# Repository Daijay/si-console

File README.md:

# SI Console

SI Console stands for Super Intelligence Console. It is a physical console that allows agentic orchestration. There is a push to talk mic, an English/Chinese toggle, LEDs, a 5 inch status screen and a monitor dashboard. This hardware project showcases the physical process of agentic orchestration, not just something that lives in your computer.

## How to use it
Press and hold the push to talk button and speak. The agents work, the LEDs show which agent is active, and the 5 inch screen shows status. Risky actions wait for you to press the green button. The red button rejects. The kill switch freezes everything. The toggle switches between English and Chinese.

## Why I made it
I wanted agents that can't just run wild. Most AI agents live in a window on your computer, and if something goes wrong, the same software that's running away has to be the thing that stops it. A software approve button has that problem. If the agent or a prompt injection controls the software, it can press the button itself. So I put approval on a real button on its own wire. Nothing in the software can press it. The kill switch is a latching switch on its own pin, and the orchestrator stops everything when it is flipped. Right now that stop is read by software, so I want to wire it in series with the green button so approval is physically impossible while the kill switch is engaged. It also makes the demo physical, because a visitor can press the big green button themselves. For low-risk actions like read-only searches, I plan to add approve on the touchscreen, so risky things need the real button and safe things stay fast. This is my first hardware project.

## Design

- Raspberry Pi 5 8GB, ULN2003 driver for the LEDs, GPIO buttons, 5 inch HDMI status screen, MSI portable monitor
- Open frame on clear laser-cut acrylic, 2 sheets. The circuit is on a custom PCB, with perfboard as a backup.
- Pin map: docs/GPIO_PIN_MAP.md

- PCB source: pcb/

## Files
- CAD assembly (STEP): blueprints/R5/si_console_assembly_R5.step
- Per-part STEP files: blueprints/R5/step/
- Fusion source: [Fusion archive (R5)](cad/si_console_R5.f3d)
- Firmware and agent code: code/
- BOM with links: bom/BOM.csv (about USD 719 including tax, the main monitor was bought by me and is not in the fundable total)

## Team
- Jayden: system, hardware, CAD, integration
- Christopher: software architecture and agent orchestration

## How I used AI
I came up with the idea and made the main decisions: the hardware, the open-frame design, and what to cut or add to stay on budget. I used AI for brainstorming, looking up part specs and prices, and Claude Code to generate first versions of the CAD scripts, wiring diagram, code and tests. I then reviewed what came out and decided what to change, keep or throw away. For example, I scrapped the boxed case because it hid the electronics.

## What's next
Christopher and I are each logging 5 to 6 hours a day while balancing IB. The plan is to get the design approved, order the parts, and finish the build by December 8, then take it to Maker Faire Shenzhen on December 11 to 14. We both want to travel there, show the project, and see Shenzhen. My biggest worry is running out of time to submit, especially waiting on design approval and parts shipping before the build.

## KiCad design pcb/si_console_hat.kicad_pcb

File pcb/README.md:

# SI Console HAT

A 2-layer, 1.6 mm Raspberry Pi 5 HAT-style carrier board (65 x 56.5 mm) that replaces the perfboard: ULN2003A LED driver, four LED resistors and a labelled screw terminal for every off-board wire. Pins follow `docs/GPIO_PIN_MAP.md`; no GPIO changed. The perfboard is the fallback, so the R5 wiring diagram (same electrical nets) was not changed.

## Connectors

| Ref | Label | Pins |
| --- | --- | --- |
| J2 | COORD | + (5 V through 150 ohm), - (OUT1, GPIO5) |
| J3 | AGENT 1 | + (100 ohm), - (OUT2, GPIO6) |
| J4 | AGENT 2 | + (100 ohm), - (OUT3, GPIO13) |
| J5 | GUARD | + (220 ohm), - (OUT4, GPIO19) |
| J6 | GREEN | SW (GPIO17), GND, L+ (5 V), L- (OUT5, GPIO20) |
| J7 | RED | SW (GPIO27), GND, L+ (5 V), L- (OUT6, GPIO21) |
| J8 | KILL | SW (GPIO22), GND, IL, IL (second NC contact, optional) |
| J9 | PTT | SW (GPIO23), GND |
| J10 | LANG | SW (GPIO24), GND |

## Optional kill interlock (off as built)

JP1 is closed and JP2 is open. To make the kill switch physically block approval, wire its second NC contact to the two IL terminals, **cut JP1**, then **solder JP2**. The contact is then in series with the green button signal. Cutting JP1 alone leaves the green button dead.

## Checks (KiCad 9.0.8)

- ERC: 0 errors, 0 warnings.
- DRC with schematic parity: 0 violations, 0 unconnected, 0 footprint errors.
- JLCPCB 2-layer rules in the .kicad_pro: 0.127 mm minimum track and clearance, 0.3 mm via drill, 0.45 mm via, 0.5 mm hole to hole, 0.3 mm copper to edge.
- `python pcb/check_nets.py`: 25 nets match `gpio_map.py`.
- Routed with Freerouting 2.5.0.

## Order from JLCPCB

1. Upload `gerbers.zip` at https://cart.jlcpcb.com/quote
2. 2 layers, 65 x 56.5 mm, qty 5, 1.6 mm, 1 oz, HASL (with lead).
3. Shipping to Canada: Global Standard Direct Line.
4. Quoted 2026-11-25 by dimensions (no file uploaded): US$4.00 boards + US$6.84 shipping = US$10.84, CAD 15.50 at 1.4296. Lead-free HASL adds US$1.20. Taxes and duties not included.

## Assembly

Solder resistors, DIP socket, then terminals. J1 is an extra-tall 2x20 female header soldered on the **underside**; trim the long pins. Mount on 16 mm M2.5 standoffs. Insert the ULN2003AN with its notch matching the silkscreen.

Optional JLCPCB assembly: `jlcpcb_bom.csv` and `jlcpcb_cpl.csv`. J1 is left out (hand fit). The DIP socket has no LCSC number yet. Check part rotations in the JLCPCB preview.

## Not verified

No board has been made or tested. Gerbers were not uploaded to JLCPCB. Active Cooler clearance is from drawings only (cooler 13.7 mm overall, header gives about 16 mm). Check that the kill switch has two NC contacts. The HAT is not modelled in the CAD. There is no HAT ID EEPROM.

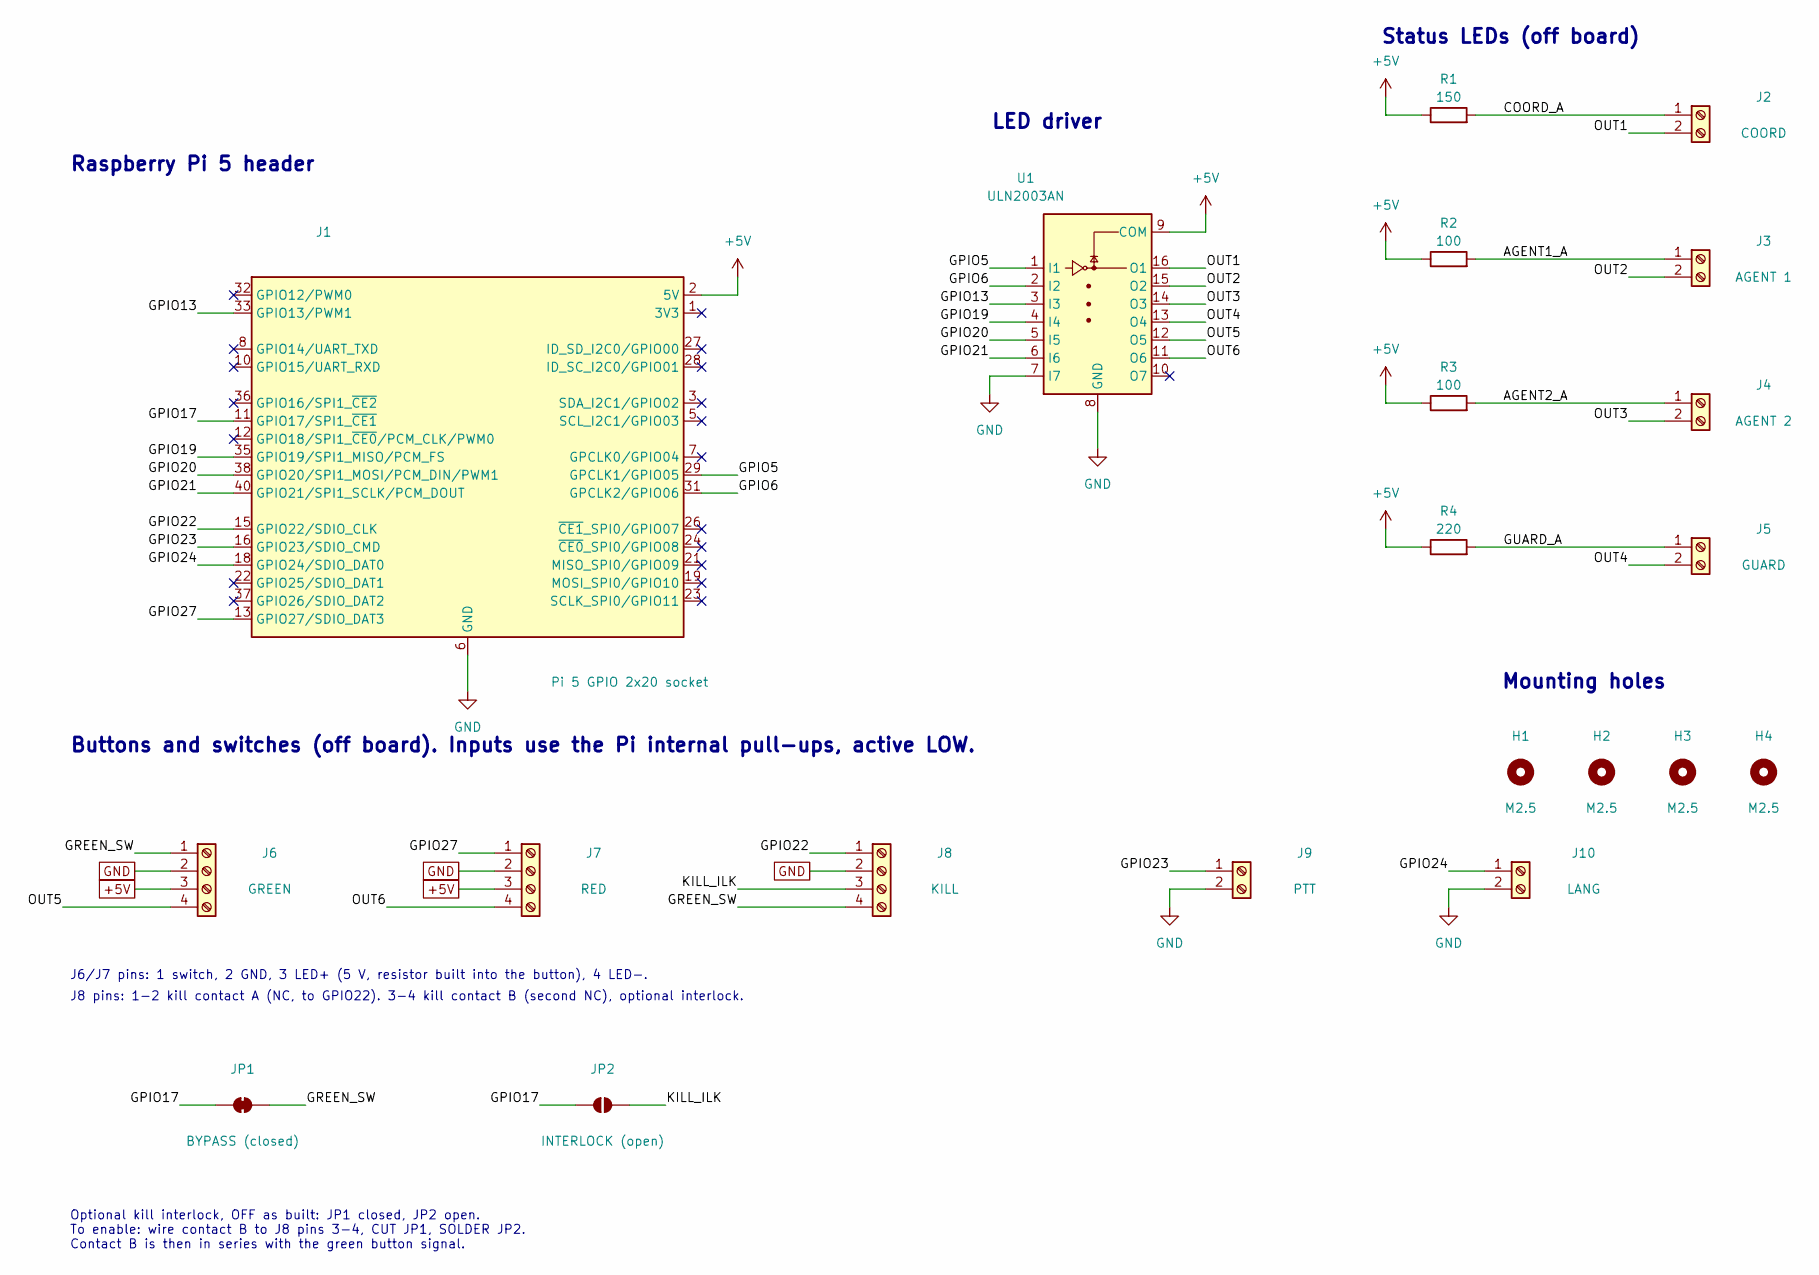
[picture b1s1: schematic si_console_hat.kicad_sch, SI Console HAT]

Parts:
H1, H2, H3, H4: M2.5; MountingHole_2.7mm_M2.5
J1: Pi 5 GPIO 2x20 socket; PinSocket_2x20_P2.54mm_Vertical; MPN Adafruit extra tall 2x20 header
J2: COORD; TerminalBlock_Phoenix_PT-1,5-2-3.5-H_1x02_P3.50mm_Horizontal; MPN Phoenix 1984617
J3: AGENT 1; TerminalBlock_Phoenix_PT-1,5-2-3.5-H_1x02_P3.50mm_Horizontal; MPN Phoenix 1984617
J4: AGENT 2; TerminalBlock_Phoenix_PT-1,5-2-3.5-H_1x02_P3.50mm_Horizontal; MPN Phoenix 1984617
J5: GUARD; TerminalBlock_Phoenix_PT-1,5-2-3.5-H_1x02_P3.50mm_Horizontal; MPN Phoenix 1984617
J6: GREEN; TerminalBlock_Phoenix_PT-1,5-4-3.5-H_1x04_P3.50mm_Horizontal; MPN Phoenix 1984633
J7: RED; TerminalBlock_Phoenix_PT-1,5-4-3.5-H_1x04_P3.50mm_Horizontal; MPN Phoenix 1984633
J8: KILL; TerminalBlock_Phoenix_PT-1,5-4-3.5-H_1x04_P3.50mm_Horizontal; MPN Phoenix 1984633
J9: PTT; TerminalBlock_Phoenix_PT-1,5-2-3.5-H_1x02_P3.50mm_Horizontal; MPN Phoenix 1984617
J10: LANG; TerminalBlock_Phoenix_PT-1,5-2-3.5-H_1x02_P3.50mm_Horizontal; MPN Phoenix 1984617
JP1: BYPASS (closed); SolderJumper-2_P1.3mm_Bridged_Pad1.0x1.5mm
JP2: INTERLOCK (open); SolderJumper-2_P1.3mm_Open_Pad1.0x1.5mm
R1: 150; R_Axial_DIN0207_L6.3mm_D2.5mm_P10.16mm_Horizontal
R2, R3: 100; R_Axial_DIN0207_L6.3mm_D2.5mm_P10.16mm_Horizontal
R4: 220; R_Axial_DIN0207_L6.3mm_D2.5mm_P10.16mm_Horizontal
U1: ULN2003AN; DIP-16_W7.62mm_Socket; MPN ULN2003AN in DIP-16 socket

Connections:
+5V: J1.2 (5V), J1.4 (5V), J6.3, J7.3, R1.1, R2.1, R3.1, R4.1, U1.9 (COM)
/AGENT1_A: J3.1, R2.2
/AGENT2_A: J4.1, R3.2
/COORD_A: J2.1, R1.2
/GPIO5: J1.29 (GPCLK1/GPIO05), U1.1 (I1)
/GPIO6: J1.31 (GPCLK2/GPIO06), U1.2 (I2)
/GPIO13: J1.33 (GPIO13/PWM1), U1.3 (I3)
/GPIO17: J1.11 (GPIO17/SPI1_~CE1), JP1.1 (A), JP2.1 (A)
/GPIO19: J1.35 (GPIO19/SPI1_MISO/PCM_FS), U1.4 (I4)
/GPIO20: J1.38 (GPIO20/SPI1_MOSI/PCM_DIN/PWM1), U1.5 (I5)
/GPIO21: J1.40 (GPIO21/SPI1_SCLK/PCM_DOUT), U1.6 (I6)
/GPIO22: J1.15 (GPIO22/SDIO_CLK), J8.1
/GPIO23: J1.16 (GPIO23/SDIO_CMD), J9.1
/GPIO24: J1.18 (GPIO24/SDIO_DAT0), J10.1
/GPIO27: J1.13 (GPIO27/SDIO_DAT3), J7.1
/GREEN_SW: J6.1, J8.4, JP1.2 (B)
/GUARD_A: J5.1, R4.2
/KILL_ILK: J8.3, JP2.2 (B)
/OUT1: J2.2, U1.16 (O1)
/OUT2: J3.2, U1.15 (O2)
/OUT3: J4.2, U1.14 (O3)
/OUT4: J5.2, U1.13 (O4)
/OUT5: J6.4, U1.12 (O5)
/OUT6: J7.4, U1.11 (O6)
GND: J1.6 (GND), J1.9 (GND), J1.14 (GND), J1.20 (GND), J1.25 (GND), J1.30 (GND), J1.34 (GND), J1.39 (GND), J6.2, J7.2, J8.2, J9.2, J10.2, U1.7 (I7), U1.8 (GND)

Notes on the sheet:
Raspberry Pi 5 header
Mounting holes
LED driver
Status LEDs (off board)
Buttons and switches (off board). Inputs use the Pi internal pull-ups, active LOW.
J6/J7 pins: 1 switch, 2 GND, 3 LED+ (5 V, resistor built into the button), 4 LED-.
J8 pins: 1-2 kill contact A (NC, to GPIO22). 3-4 kill contact B (second NC), optional interlock.
Optional kill interlock, OFF as built: JP1 closed, JP2 open. To enable: wire contact B to J8 pins 3-4, CUT JP1, SOLDER JP2. Contact B is then in series with the green button signal.

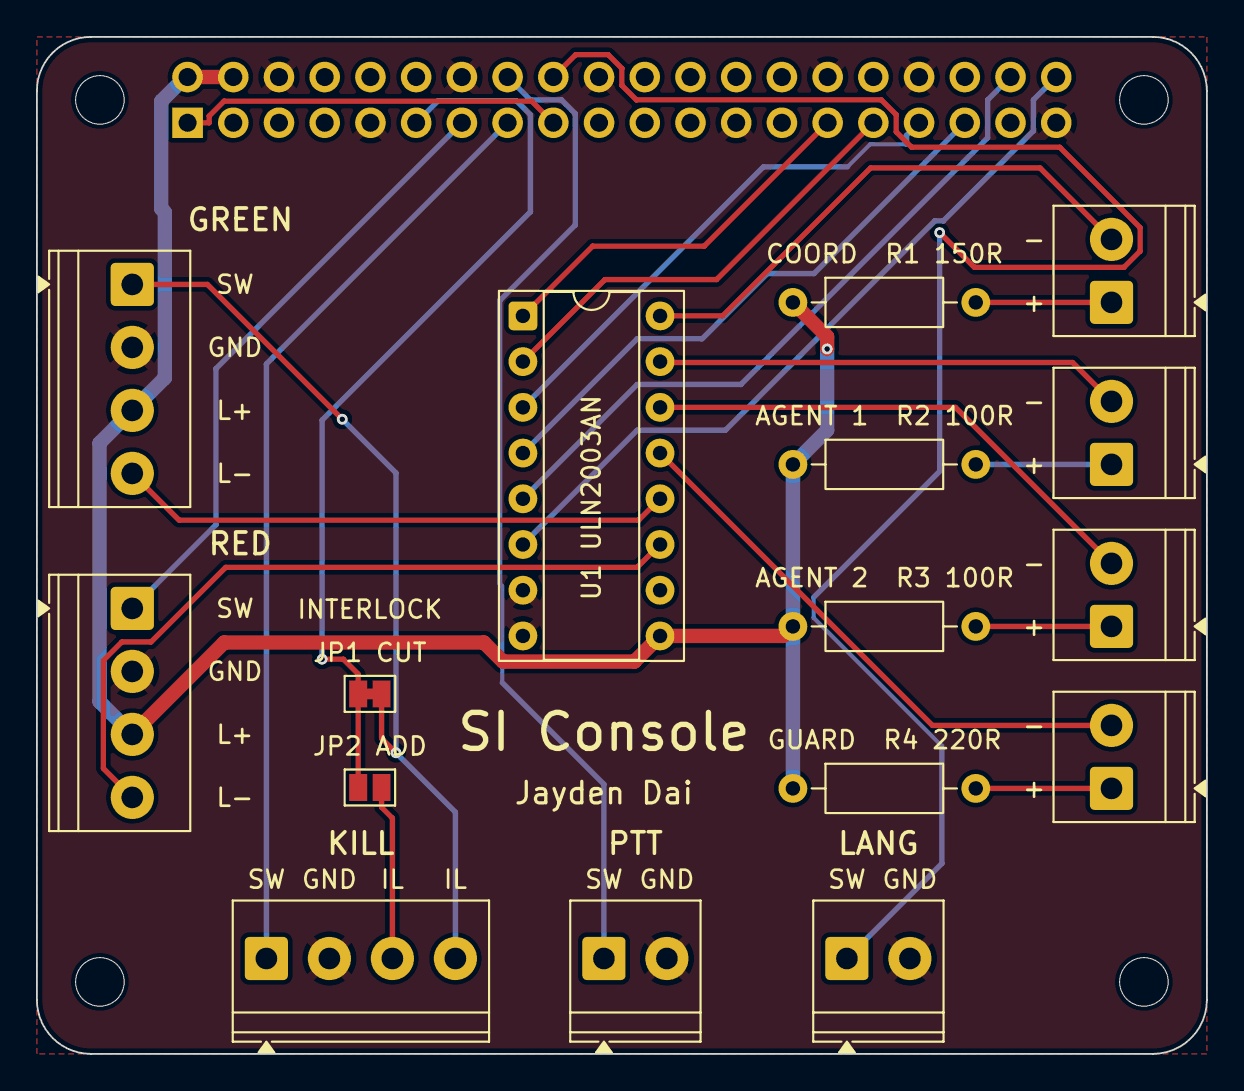
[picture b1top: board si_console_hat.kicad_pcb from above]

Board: 2 copper layers, 65.0 x 56.5 mm, 21 parts (1 on the bottom side), 25 nets.

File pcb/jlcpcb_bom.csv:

Comment,Designator,Footprint,LCSC Part #
Screw terminal 3.5mm,"J10,J2,J3,J4,J5,J9","TerminalBlock_Phoenix_PT-1,5-2-3.5-H_1x02_P3.50mm_Horizontal",C3819527
Screw terminal 3.5mm,"J6,J7,J8","TerminalBlock_Phoenix_PT-1,5-4-3.5-H_1x04_P3.50mm_Horizontal",C5144867
150 ohm,R1,R_Axial_DIN0207_L6.3mm_D2.5mm_P10.16mm_Horizontal,C119307
100 ohm,"R2,R3",R_Axial_DIN0207_L6.3mm_D2.5mm_P10.16mm_Horizontal,C2903231
220 ohm,R4,R_Axial_DIN0207_L6.3mm_D2.5mm_P10.16mm_Horizontal,C127220
DIP-16 socket,U1,DIP-16_W7.62mm_Socket,

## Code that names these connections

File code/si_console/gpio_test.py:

# GPIO test script. Run this on the Pi before connecting the bridge
# program. It tests buttons, LEDs through the ULN2003, the kill
# switch, and the language toggle, one at a time, with plain output.
# Usage on the Pi: python3 -m si_console.gpio_test
# Run it on a breadboard first. Solder later. Do not run it on a
# laptop. It needs real GPIO. It needs gpiozero, which does not work
# on a laptop. On a laptop it will fail at import, and that is fine.
# GPIO map imported from si_console/gpio_map.py. That file is the
# single source of truth for pins. Do not copy pin numbers here. The
# status LED names are COORD, AGENT 1, AGENT 2, GUARD. COORD is
# GPIO5, AGENT 1 is GPIO6, AGENT 2 is GPIO13, GUARD is GPIO19.
# All 6 LEDs run through the ULN2003. GPIO26 is free. ULN2003 IN7 is
# tied to GND.
# Buttons are inputs, GPIO to ground, internal pull up, active low.
# Green approve GPIO17, physical pin 11. Red reject GPIO27, pin 13.
# Kill freeze GPIO22, physical pin 15, wired normally closed.
# Push to talk GPIO23, physical pin 16.
# Language toggle GPIO24, physical pin 18.
# LEDs are outputs to ULN2003 inputs, not direct to LEDs. The
# ULN2003 inverts the signal and sinks current only. Its output is
# open collector. It pulls down to ground when its input is HIGH.
# It never drives HIGH. The LED path is 5V, then resistor, then LED
# anode, then LED cathode to the ULN2003 output, then chip GND.
# GPIO HIGH turns the LED on. GPIO LOW turns it off.
# ULN2003 pinout, VERIFIED from the datasheet: inputs pins 1 to 7,
# GND pin 8, COM pin 9 to the 5V load rail, outputs pins 16 to 10
# in reverse order. IN1 drives OUT1, IN2 drives OUT2, and so on.
# Channel map:
#   Ch1 IN1 pin 1 from GPIO5, OUT1 pin 16 to COORD LED, green, 150 ohm
#   Ch2 IN2 pin 2 from GPIO6, OUT2 pin 15 to AGENT 1 LED, white, 100 ohm
#   Ch3 IN3 pin 3 from GPIO13, OUT3 pin 14 to AGENT 2 LED, blue, 100 ohm
#   Ch4 IN4 pin 4 from GPIO19, OUT4 pin 13 to GUARD LED, yellow, 220 ohm
#   Ch5 IN5 pin 5 from GPIO20, OUT5 pin 12 to green button LED
#   Ch6 IN6 pin 6 from GPIO21, OUT6 pin 11 to red button LED
#   Ch7 spare. IN7 pin 7 tied to GND. Do not leave it floating.
# Resistor math: see docs/GPIO_PIN_MAP.md. Every Vf is ASSUMED.
# Measure the current with a multimeter on the bench. Do not guess.
# Button LEDs run from 5V through their built-in resistors. Do not add
# another resistor.
# ULN2003 input at 3.3V is test first, not guaranteed. The chip is
# sized for 5V TTL logic. Bench test every channel at 3.3V before
# soldering. If a channel is dim or warm, use a different driver,
# for example a logic level MOSFET per LED, or a TBD62083A, which is
# a 3.3V friendly Darlington array, LIKELY. Do not solder first.
# Kill switch logic: not pressed, NC closed, GPIO22 reads LOW,
# normal. Pressed and latched, NC open, GPIO22 reads HIGH, frozen.
# A broken wire also reads HIGH, frozen. That is fail safe. Test
# with a multimeter before trusting code. Poll every 100 ms. Do not
# rely on an edge event only.
# Debounce: gpiozero Button with bounce_time 0.05 s for green, red,
# and push to talk. Kill switch bounce_time 0.02 s. Test with 100
# button presses, no double execution. Use gpiozero, not RPi.GPIO.
# RPi.GPIO does not work on Pi 5.
"""GPIO test script. Buttons, LEDs via ULN2003, kill, toggle."""

from __future__ import annotations

import time

# GPIO map, Rev R2. Imported, not copied. gpio_map.py is the truth.
from si_console.gpio_map import (
    BUTTON_LEDS,
    GREEN_BUTTON,
    DEBOUNCE_SECONDS,
    KILL_DEBOUNCE_SECONDS,
    KILL_POLL_SECONDS,
    KILL_SWITCH,
    LANG_TOGGLE,
    PTT_BUTTON,
    RED_BUTTON,
    STATUS_LEDS,
)


def test_leds() -> None:
    """Turn on each LED for 1 second, in order. Watch each one.
    If a LED stays dark, check the resistor, the LED direction, the
    ULN2003 channel, and the 5V rail, in that order. If a LED is
    dim, check the resistor value and the 3.3V input to the ULN2003.
    If the chip is warm, stop. Check COM pin 9 to 5V, GND pin 8 to
    GND, and that no output is tied to 5V."""
    from gpiozero import LED

    print("LED test. Each LED should light for 1 second.")
    for name, pin in {**STATUS_LEDS, **BUTTON_LEDS}.items():
        print(f"  {name} GPIO{pin} on")
        led = LED(pin)
        led.on()
        time.sleep(1)
        led.off()
        led.close()
    print("LED test done. All LEDs off.")


def test_buttons() -> None:
    """Press each button once when asked. Prints what it saw.
    Green and red are active low. Kill is LOW normal, HIGH frozen.
    The toggle is read on change. Press Ctrl+C to stop."""
    from gpiozero import Button

    print("Button test. Press each button when asked. Ctrl+C to stop.")
    green = Button(GREEN_BUTTON, bounce_time=DEBOUNCE_SECONDS)
    red = Button(RED_BUTTON, bounce_time=DEBOUNCE_SECONDS)
    ptt = Button(PTT_BUTTON, bounce_time=DEBOUNCE_SECONDS)
    kill = Button(KILL_SWITCH, bounce_time=KILL_DEBOUNCE_SECONDS)
    lang = Button(LANG_TOGGLE, bounce_time=DEBOUNCE_SECONDS)
    try:
        input("Press green, then Enter: ")
        print(f"  green pressed: {green.is_pressed} (expect True)")
        input("Press red, then Enter: ")
        print(f"  red pressed: {red.is_pressed} (expect True)")
        input("Hold push to talk, then Enter: ")
        print(f"  push to talk held: {ptt.is_pressed} (expect True)")
        print(f"  kill frozen (HIGH): {kill.is_pressed} (expect False when normal)")
        print(f"  toggle state: {lang.is_pressed} (EN or ZH, label the switch)")
    finally:
        green.close()
        red.close()
        ptt.close()
        kill.close()
        lang.close()
    print("Button test done.")


def test_kill_loop(seconds: int = 10) -> None:
    """Poll the kill switch every 100 ms for N seconds. Print the
    state each time it changes. Press and release the kill switch
    during the test. A missed edge must not miss a kill, so polling
    is the rule, not edge events only."""
    from gpiozero import Button

    print(f"Kill poll test for {seconds} seconds. Press and release kill.")
    kill = Button(KILL_SWITCH, bounce_time=KILL_DEBOUNCE_SECONDS)
    last = kill.is_pressed
    print(f"  start frozen: {last} (expect False)")
    end = time.time() + seconds
    while time.time() < end:
        now = kill.is_pressed
        if now != last:
            print(f"  kill changed to frozen: {now}")
            last = now
        time.sleep(KILL_POLL_SECONDS)
    kill.close()
    print("Kill poll test done.")


def test_100_presses() -> None:
    """Press green 100 times. Counts presses. No double execution
    means the count is 100, not more. If one press counts twice,
    raise bounce_time from 0.05 s to 0.1 s and test again."""
    from gpiozero import Button

    print("100 press test. Press green 100 times, then Ctrl+C.")
    green = Button(GREEN_BUTTON, bounce_time=DEBOUNCE_SECONDS)
    count = [0]

    def on_press() -> None:
        count[0] += 1
        if count[0] % 10 == 0:
            print(f"  count {count[0]}")

    green.when_pressed = on_press
    try:
        while count[0] < 100:
            time.sleep(KILL_POLL_SECONDS)
    except KeyboardInterrupt:
        pass
    finally:
        green.close()
    print(f"100 press test done. Count: {count[0]} (expect 100).")


def main() -> None:
    """Run all tests in order: LEDs, buttons, kill poll."""
    import sys

    which = sys.argv[1] if len(sys.argv) > 1 else "all"
    if which in ("all", "leds"):
        test_leds()
    if which in ("all", "buttons"):
        test_buttons()
    if which in ("all", "kill"):
        test_kill_loop()
    if which == "presses":
        test_100_presses()
    print("GPIO test done.")


if __name__ == "__main__":
    main()
